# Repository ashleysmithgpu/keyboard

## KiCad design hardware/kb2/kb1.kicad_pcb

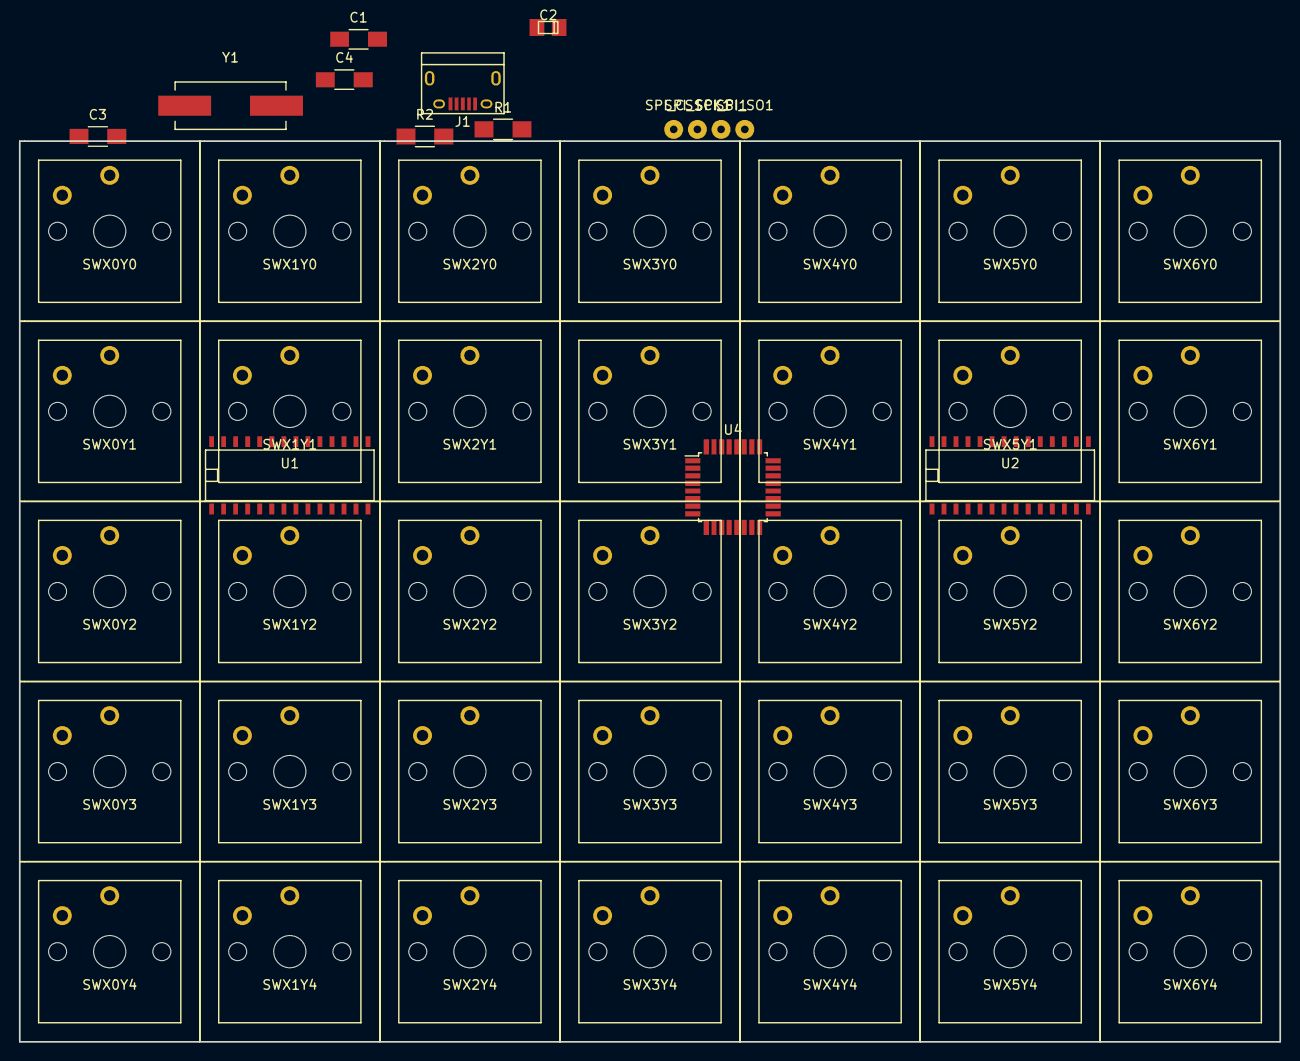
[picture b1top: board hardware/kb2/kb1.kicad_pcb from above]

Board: 2 copper layers, 133.0 x 95.0 mm, 50 parts (0 on the bottom side), 50 nets, no tracks yet.

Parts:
C1: 1uF; C_1206_HandSoldering
C2: 10uF; TantalC_SizeR_EIA-2012
C3, C4: 12-22pF; C_1206_HandSoldering
J1: USB_B_Micro; USB_Micro-B
R1, R2: 22; R_1206_HandSoldering
SPI_CS1: C3; SolderWirePad_single_0-8mmDrill
SPI_SCK1: C4; SolderWirePad_single_0-8mmDrill
SPI_SI1: C5; SolderWirePad_single_0-8mmDrill
SPI_SO1: C6; SolderWirePad_single_0-8mmDrill
SWX0Y0, SWX0Y1, SWX0Y2, SWX0Y3, SWX0Y4, SWX1Y0, SWX1Y1, SWX1Y2, SWX1Y3, SWX1Y4, SWX2Y0, SWX2Y1, SWX2Y2, SWX2Y3, SWX2Y4, SWX3Y0, SWX3Y1, SWX3Y2, SWX3Y3, SWX3Y4, SWX4Y0, SWX4Y1, SWX4Y2, SWX4Y3, SWX4Y4, SWX5Y0, SWX5Y1, SWX5Y2, SWX5Y3, SWX5Y4, SWX6Y0, SWX6Y1, SWX6Y2, SWX6Y3, SWX6Y4: PG135001D01
U1, U2: MCP23S17; SOIC-28
U4: ATMEGA32U2-AU; TQFP-32_7x7mm_Pitch0.8mm
Y1: 8 MHz; Crystal_HC49-SD_SMD

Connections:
unnamed: C1.1, C2.2, C3.1, C4.1, J1.5, U1.10, U1.15, U1.16, U1.17, U2.10, U2.16, U2.17, U4.3, U4.28
unnamed: C1.2, U4.27
unnamed: C2.1, J1.1, SWX0Y0.1, SWX0Y1.1, SWX0Y2.1, SWX0Y3.1, SWX0Y4.1, SWX1Y0.1, SWX1Y1.1, SWX1Y2.1, SWX1Y3.1, SWX1Y4.1, SWX2Y0.1, SWX2Y1.1, SWX2Y2.1, SWX2Y3.1, SWX2Y4.1, SWX3Y0.1, SWX3Y1.1, SWX3Y2.1, SWX3Y3.1, SWX3Y4.1, SWX4Y0.1, SWX4Y1.1, SWX4Y2.1, SWX4Y3.1, SWX4Y4.1, SWX5Y0.1, SWX5Y1.1, SWX5Y2.1, SWX5Y3.1, SWX5Y4.1, SWX6Y0.1, SWX6Y1.1, SWX6Y2.1, SWX6Y3.1, SWX6Y4.1, U1.9, U1.18, U2.9, U2.15, U2.18, U4.4, U4.31, U4.32
unnamed: C3.2, U4.2, Y1.1
unnamed: C4.2, U4.1, Y1.2
unnamed: J1.2, R1.1
unnamed: J1.3, R2.1
unnamed: R1.2, U4.30
unnamed: R2.2, U4.29
unnamed: SPI_CS1.1, U1.11, U2.11
unnamed: SPI_SCK1.1, U1.12, U2.12, U4.15
unnamed: SPI_SI1.1, U1.13, U2.13, U4.16
unnamed: SPI_SO1.1, U1.14, U2.14, U4.17
unnamed: SWX0Y0.2, U1.1
unnamed: SWX0Y1.2, U1.2
unnamed: SWX0Y2.2, U1.3
unnamed: SWX0Y3.2, U1.4
unnamed: SWX0Y4.2, U1.5
unnamed: SWX1Y0.2, U1.6
unnamed: SWX1Y1.2, U1.7
unnamed: SWX1Y2.2, U1.8
unnamed: SWX1Y3.2, U1.21
unnamed: SWX1Y4.2, U1.22
unnamed: SWX2Y0.2, U1.23
unnamed: SWX2Y1.2, U1.24
unnamed: SWX2Y2.2, U1.25
unnamed: SWX2Y3.2, U1.26
unnamed: SWX2Y4.2, U1.27
unnamed: SWX3Y0.2, U1.28
unnamed: SWX3Y1.2, U2.1
unnamed: SWX3Y2.2, U2.2
unnamed: SWX3Y3.2, U2.3
unnamed: SWX3Y4.2, U2.4
unnamed: SWX4Y0.2, U2.5
unnamed: SWX4Y1.2, U2.6
unnamed: SWX4Y2.2, U2.7
unnamed: SWX4Y3.2, U2.8
unnamed: SWX4Y4.2, U2.21
unnamed: SWX5Y0.2, U2.22
unnamed: SWX5Y1.2, U2.23
unnamed: SWX5Y2.2, U2.24
unnamed: SWX5Y3.2, U2.25
unnamed: SWX5Y4.2, U2.26
unnamed: SWX6Y0.2, U2.27
unnamed: SWX6Y1.2, U2.28
unnamed: SWX6Y2.2, U4.13
unnamed: SWX6Y3.2, U4.12
unnamed: SWX6Y4.2, U4.11
unnamed: U1.19, U1.20, U4.6
unnamed: U2.19, U2.20, U4.7

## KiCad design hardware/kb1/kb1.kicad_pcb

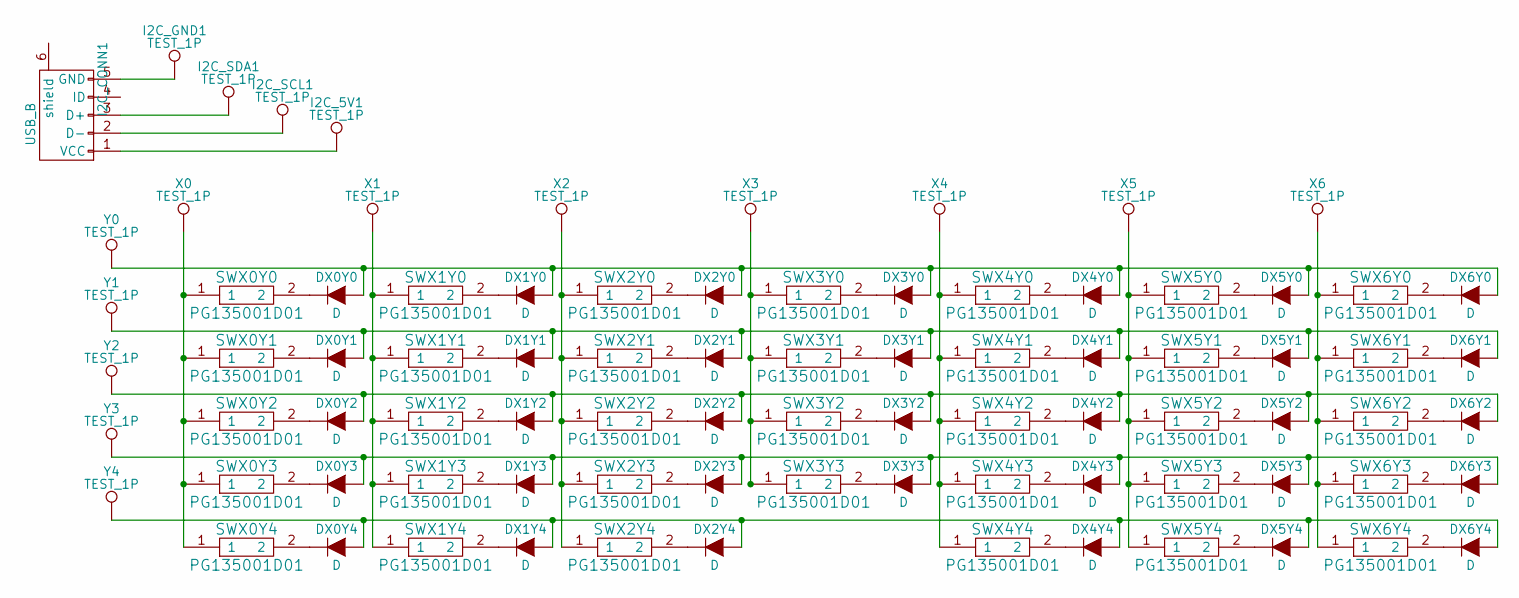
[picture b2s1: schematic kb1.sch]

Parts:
DX0Y0, DX0Y1, DX0Y2, DX0Y3, DX0Y4, DX1Y0, DX1Y1, DX1Y2, DX1Y3, DX1Y4, DX2Y0, DX2Y1, DX2Y2, DX2Y3, DX2Y4, DX3Y0, DX3Y1, DX3Y2, DX3Y3, DX4Y0, DX4Y1, DX4Y2, DX4Y3, DX4Y4, DX5Y0, DX5Y1, DX5Y2, DX5Y3, DX5Y4, DX6Y0, DX6Y1, DX6Y2, DX6Y3, DX6Y4: D; Diode_DO-35_SOD27_Horizontal_RM10
I2C_5V1, I2C_GND1, I2C_SCL1, I2C_SDA1: TEST_1P; SolderWirePad_single_0-8mmDrill
I2C_CONN1: USB_B; USB_Micro-B
SWX0Y0, SWX0Y1, SWX0Y2, SWX0Y3, SWX0Y4, SWX1Y0, SWX1Y1, SWX1Y2, SWX1Y3, SWX1Y4, SWX2Y0, SWX2Y1, SWX2Y2, SWX2Y3, SWX2Y4, SWX3Y0, SWX3Y1, SWX3Y2, SWX3Y3, SWX4Y0, SWX4Y1, SWX4Y2, SWX4Y3, SWX4Y4, SWX5Y0, SWX5Y1, SWX5Y2, SWX5Y3, SWX5Y4, SWX6Y0, SWX6Y1, SWX6Y2, SWX6Y3, SWX6Y4: PG135001D01
X0, X1, X2, X3, X4, X5, X6: TEST_1P; SolderWirePad_single_0-8mmDrill
Y0, Y1, Y2, Y3, Y4: TEST_1P; SolderWirePad_single_0-8mmDrill

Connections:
unnamed: DX0Y0.1 (K), SWX0Y0.2
unnamed: DX0Y0.2 (A), DX1Y0.2 (A), DX2Y0.2 (A), DX3Y0.2 (A), DX4Y0.2 (A), DX5Y0.2 (A), DX6Y0.2 (A), Y0.1
unnamed: DX0Y1.1 (K), SWX0Y1.2
unnamed: DX0Y1.2 (A), DX1Y1.2 (A), DX2Y1.2 (A), DX3Y1.2 (A), DX4Y1.2 (A), DX5Y1.2 (A), DX6Y1.2 (A), Y1.1
unnamed: DX0Y2.1 (K), SWX0Y2.2
unnamed: DX0Y2.2 (A), DX1Y2.2 (A), DX2Y2.2 (A), DX3Y2.2 (A), DX4Y2.2 (A), DX5Y2.2 (A), DX6Y2.2 (A), Y2.1
unnamed: DX0Y3.1 (K), SWX0Y3.2
unnamed: DX0Y3.2 (A), DX1Y3.2 (A), DX2Y3.2 (A), DX3Y3.2 (A), DX4Y3.2 (A), DX5Y3.2 (A), DX6Y3.2 (A), Y3.1
unnamed: DX0Y4.1 (K), SWX0Y4.2
unnamed: DX0Y4.2 (A), DX1Y4.2 (A), DX2Y4.2 (A), DX4Y4.2 (A), DX5Y4.2 (A), DX6Y4.2 (A), Y4.1
unnamed: DX1Y0.1 (K), SWX1Y0.2
unnamed: DX1Y1.1 (K), SWX1Y1.2
unnamed: DX1Y2.1 (K), SWX1Y2.2
unnamed: DX1Y3.1 (K), SWX1Y3.2
unnamed: DX1Y4.1 (K), SWX1Y4.2
unnamed: DX2Y0.1 (K), SWX2Y0.2
unnamed: DX2Y1.1 (K), SWX2Y1.2
unnamed: DX2Y2.1 (K), SWX2Y2.2
unnamed: DX2Y3.1 (K), SWX2Y3.2
unnamed: DX2Y4.1 (K), SWX2Y4.2
unnamed: DX3Y0.1 (K), SWX3Y0.2
unnamed: DX3Y1.1 (K), SWX3Y1.2
unnamed: DX3Y2.1 (K), SWX3Y2.2
unnamed: DX3Y3.1 (K), SWX3Y3.2
unnamed: DX4Y0.1 (K), SWX4Y0.2
unnamed: DX4Y1.1 (K), SWX4Y1.2
unnamed: DX4Y2.1 (K), SWX4Y2.2
unnamed: DX4Y3.1 (K), SWX4Y3.2
unnamed: DX4Y4.1 (K), SWX4Y4.2
unnamed: DX5Y0.1 (K), SWX5Y0.2
unnamed: DX5Y1.1 (K), SWX5Y1.2
unnamed: DX5Y2.1 (K), SWX5Y2.2
unnamed: DX5Y3.1 (K), SWX5Y3.2
unnamed: DX5Y4.1 (K), SWX5Y4.2
unnamed: DX6Y0.1 (K), SWX6Y0.2
unnamed: DX6Y1.1 (K), SWX6Y1.2
unnamed: DX6Y2.1 (K), SWX6Y2.2
unnamed: DX6Y3.1 (K), SWX6Y3.2
unnamed: DX6Y4.1 (K), SWX6Y4.2
unnamed: I2C_5V1.1, I2C_CONN1.1 (VCC)
unnamed: I2C_CONN1.2 (D-), I2C_SCL1.1
unnamed: I2C_CONN1.3 (D+), I2C_SDA1.1
unnamed: I2C_CONN1.5 (GND), I2C_GND1.1
unnamed: SWX0Y0.1, SWX0Y1.1, SWX0Y2.1, SWX0Y3.1, SWX0Y4.1, X0.1
unnamed: SWX1Y0.1, SWX1Y1.1, SWX1Y2.1, SWX1Y3.1, SWX1Y4.1, X1.1
unnamed: SWX2Y0.1, SWX2Y1.1, SWX2Y2.1, SWX2Y3.1, SWX2Y4.1, X2.1
unnamed: SWX3Y0.1, SWX3Y1.1, SWX3Y2.1, SWX3Y3.1, X3.1
unnamed: SWX4Y0.1, SWX4Y1.1, SWX4Y2.1, SWX4Y3.1, SWX4Y4.1, X4.1
unnamed: SWX5Y0.1, SWX5Y1.1, SWX5Y2.1, SWX5Y3.1, SWX5Y4.1, X5.1
unnamed: SWX6Y0.1, SWX6Y1.1, SWX6Y2.1, SWX6Y3.1, SWX6Y4.1, X6.1

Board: 2 copper layers, 85 parts (0 on the bottom side), 50 nets, no tracks yet.

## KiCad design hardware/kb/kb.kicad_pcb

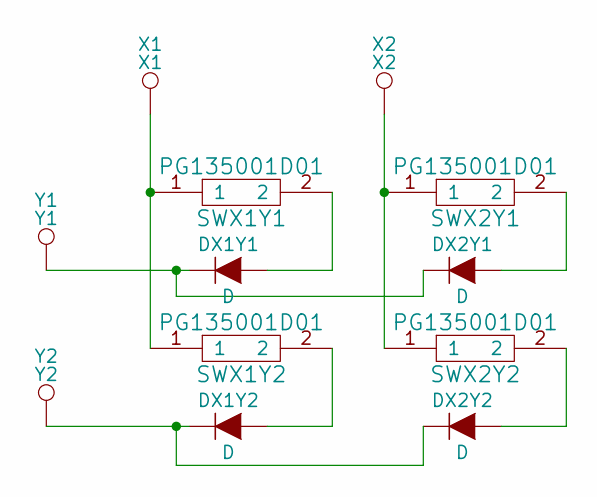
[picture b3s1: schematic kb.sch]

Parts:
DX1Y1, DX1Y2, DX2Y1, DX2Y2: D; Diode_DO-35_SOD27_Horizontal_RM10
SWX1Y1, SWX1Y2, SWX2Y1, SWX2Y2: PG135001D01
X1: X1; SolderWirePad_single_0-8mmDrill
X2: X2; SolderWirePad_single_0-8mmDrill
Y1: Y1; SolderWirePad_single_0-8mmDrill
Y2: Y2; SolderWirePad_single_0-8mmDrill

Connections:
unnamed: DX1Y1.1 (K), DX2Y1.1 (K), Y1.1
unnamed: DX1Y1.2 (A), SWX1Y1.2
unnamed: DX1Y2.1 (K), DX2Y2.1 (K), Y2.1
unnamed: DX1Y2.2 (A), SWX1Y2.2
unnamed: DX2Y1.2 (A), SWX2Y1.2
unnamed: DX2Y2.2 (A), SWX2Y2.2
unnamed: SWX1Y1.1, SWX1Y2.1, X1.1
unnamed: SWX2Y1.1, SWX2Y2.1, X2.1

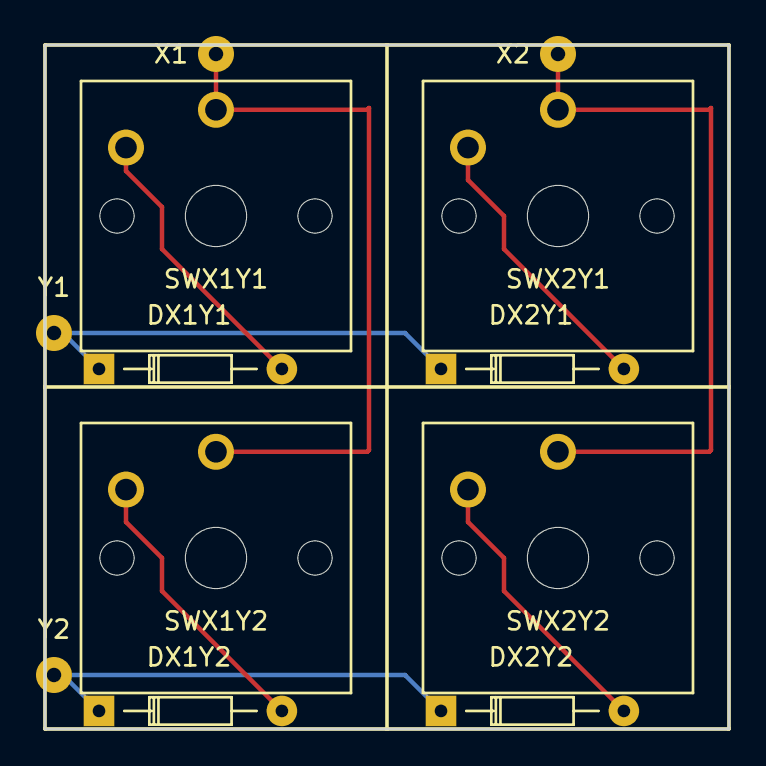
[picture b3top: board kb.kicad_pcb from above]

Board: 2 copper layers, 38.0 x 38.0 mm, 12 parts (0 on the bottom side), 8 nets.

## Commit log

2016-04-20 first try at keyboard design
2016-04-20 changed to red for cutting colour
2016-04-21 Added design files and source files
2016-04-21 Moved text to txt file
2016-04-27 Added initial eagle files
2016-04-28 Updated distances from dimensions
2016-04-28 Moved files around, added version sent for fabrication, added module for i2c lhs
2016-04-29 Added multiplexer design
2016-10-20 - Updated keys, added i2c interface
2016-10-21 - Added i2c code, keymapping code, master/slave code
2016-10-27 - Compiling version, not tested yet
2016-10-28 - Added plate for switches
2017-09-26 New keyboard for low profile kailh
2017-10-31 Changed to using io expanders
2017-11-16 Adding low profile keyboard
2017-11-21 Added kailh switch footprint
2017-11-21 Added kailh switch pdfs
2017-11-23 Adding spaces for clicky version of kailh switch
